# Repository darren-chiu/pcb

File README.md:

<b> PCB Repository meant to track and hold my PCB designs along with any code associated </b> <br/> <br/>
 Astromech Board -- STM32f405 and MPU6050 with darlington arrays for driving steppers

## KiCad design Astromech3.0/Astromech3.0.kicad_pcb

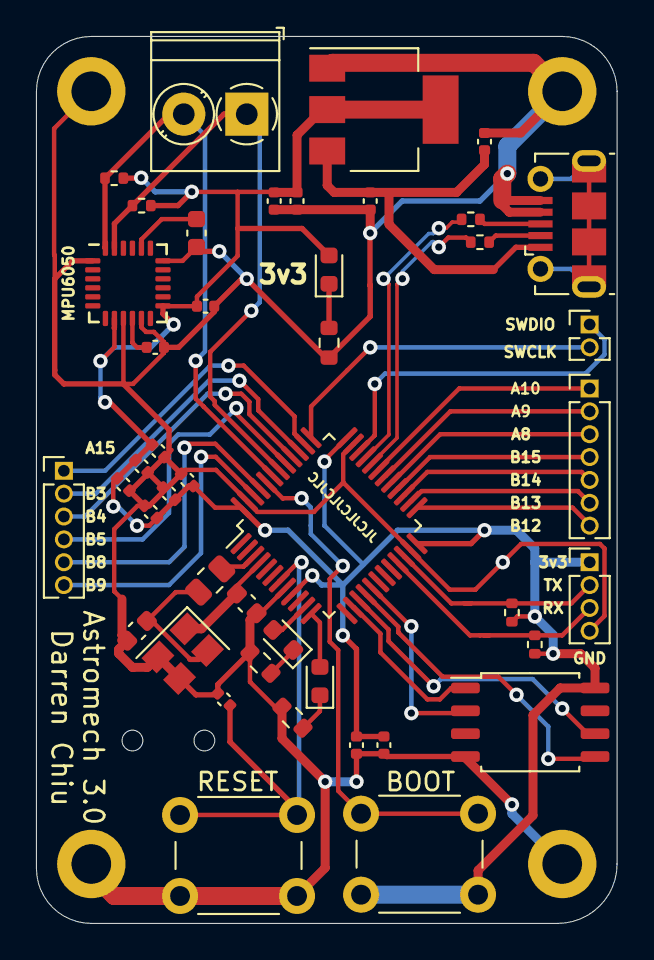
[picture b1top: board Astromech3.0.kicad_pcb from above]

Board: 2 copper layers, 32.3 x 49.3 mm, 48 parts (0 on the bottom side), 42 nets.

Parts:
C1, C4, C5, C6, C7, C9, C10, C11, C12: 100nF; C_0402_1005Metric
C2, C3: 12p; C_0603_1608Metric
C8, C17: 10uF; C_0402_1005Metric
C13, C15, C18, C19: 0.1uF; C_0402_1005Metric
C16: 2.2nF; C_0603_1608Metric
D1: RED; D_0603_1608Metric
D2: YELLOW; D_0603_1608Metric
D3: GREEN; D_0603_1608Metric
H1, H2, H3, H4: MountingHole_Pad; MountingHole_2.2mm_M2_DIN965_Pad
J1: Screw_Terminal_01x02; TerminalBlock_Phoenix_PT-1,5-2-3.5-H_1x02_P3.50mm_Horizontal
J2: Conn_01x02; PinHeader_1x02_P1.27mm_Vertical
J3: USB_B_Micro; USB_Micro-B_Molex-105017-0001
J4: Conn_01x04; PinHeader_1x04_P1.27mm_Vertical
J5: Conn_01x07; PinHeader_1x07_P1.27mm_Vertical
J6: Conn_01x06; PinHeader_1x06_P1.27mm_Vertical
R1, R2, R3, R4: 10k; R_0402_1005Metric
R5: 220; R_0805_2012Metric
R6, R7, R10: 510; R_0603_1608Metric
R8, R9: 22; R_0402_1005Metric
SW1, SW2: SW_Push; SW_PUSH_6mm
U1: STM32F103C8Tx; LQFP-48_7x7mm_P0.5mm
U2: MPU-6050; InvenSense_QFN-24_4x4mm_P0.5mm
U3: AMS1117; SOT-223-3_TabPin2
U4: W25Q128JVS; SOIC-8_5.23x5.23mm_P1.27mm
Y1: Crystal; Crystal_SMD_3225-4Pin_3.2x2.5mm

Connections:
+3V3: C1.1, C4.1, C5.1, C6.1, C7.1, C9.1, C11.1, C13.2, C17.1, C18.2, C19.2, D1.2, J4.1, R1.2, R2.2, R3.2, R4.2, SW2.2, U1.9, U1.24, U1.36, U1.48, U2.8, U2.13, U3.2, U4.8
+5V: C8.1, C12.1, J3.1, U3.3
BOOT0: SW2.1, U1.44
D+: R8.1, U1.33
D-: R9.1, U1.32
GND: C1.2, C2.1, C3.1, C4.2, C5.2, C6.2, C7.2, C8.2, C9.2, C10.2, C11.2, C12.2, C13.1, C15.1, C16.1, C17.2, C18.1, C19.1, H1.1, H2.1, H3.1, H4.1, J3.4, J3.5, J4.4, R6.1, R7.1, R10.1, SW1.1, U1.8, U1.23, U1.35, U1.47, U2.1, U2.9, U2.11, U2.18, U3.1, U4.4, Y1.2, Y1.3
I2C_SCL: J1.1, R3.1, U1.42, U2.23
I2C_SDA: J1.2, R4.1, U1.43, U2.24
unnamed: C2.2, R5.2, Y1.4
unnamed: C15.2, U2.10
unnamed: C16.2, U2.20
unnamed: D1.1, R6.2
unnamed: D2.1, R7.2
unnamed: D3.1, R10.2
unnamed: J3.2, R9.2
unnamed: J3.3, R8.2
OSC_IN: R5.1, U1.3
OSC_OUT: C3.2, U1.4, Y1.1
PA8: J5.3, U1.29
PA9: J5.2, U1.30
PA10: J5.1, U1.31
PA15: J6.1, U1.38
PB3: J6.2, U1.39
PB4: J6.3, U1.40
PB5: J6.4, U1.41
PB8: J6.5, U1.45
PB9: J6.6, U1.46
PB12: J5.7, U1.25
PB13: J5.6, U1.26
PB14: J5.5, U1.27
PB15: J5.4, U1.28
QSPI_CLK: U1.15, U4.6
QSPI_CS: U1.14, U4.1
RESET: C10.1, SW1.2, U1.7
SPI_MISO: U1.16, U4.5
SPI_MOSI: U1.17, U4.2
STATUS0: D3.2, U1.12
STATUS1: D2.2, U1.11
SWCLK: J2.2, U1.37
SWDIO: J2.1, U1.34
UART_RX: J4.3, R2.1, U1.21
UART_TX: J4.2, R1.1, U1.22

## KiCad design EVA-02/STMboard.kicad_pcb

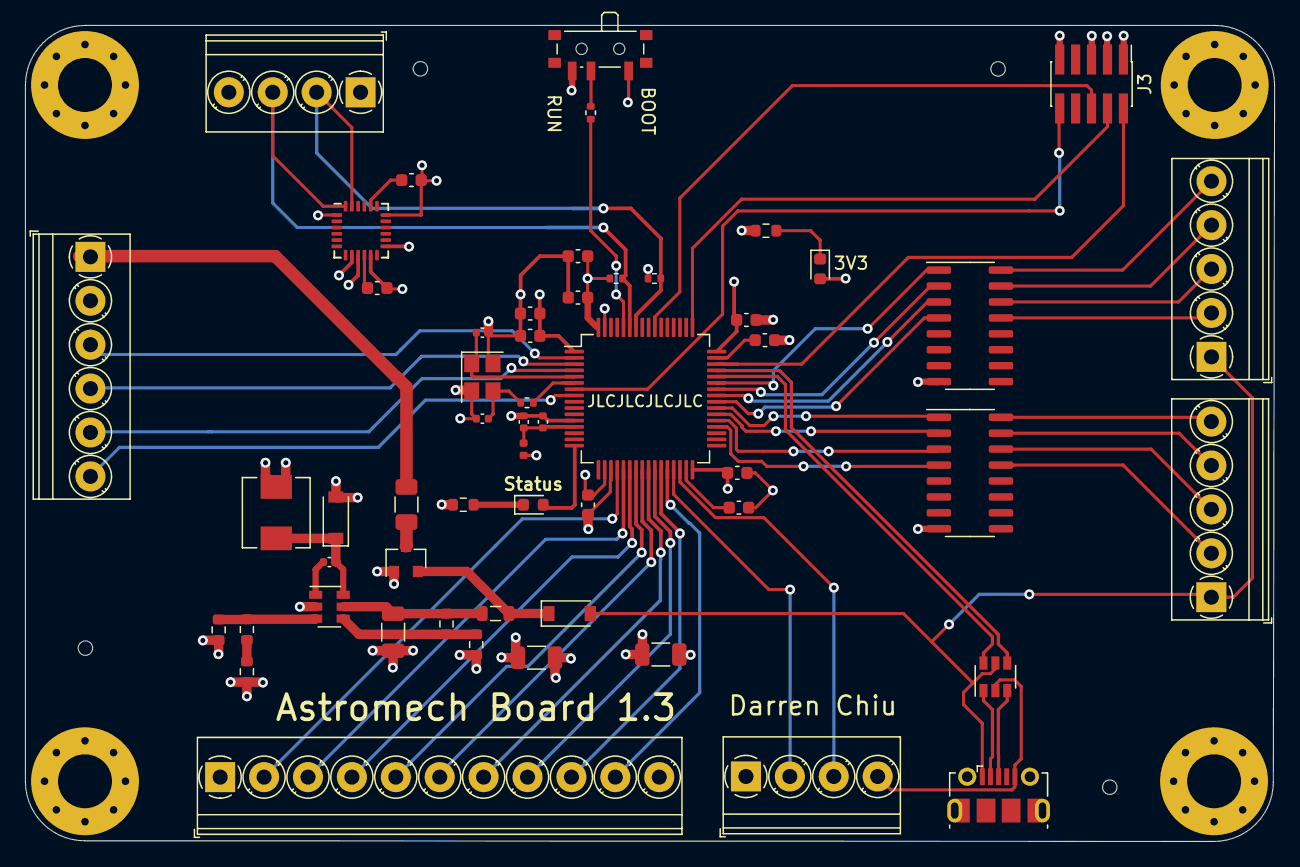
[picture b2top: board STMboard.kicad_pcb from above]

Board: 4 copper layers, 99.6 x 65.1 mm, 59 parts (0 on the bottom side), 66 nets.

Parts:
C1: 4u7; C_0603_1608Metric
C2, C4: 2.2u; C_0603_1608Metric
C3, C5, C6, C8, C9, C10, C11: 100nF; C_0603_1608Metric
C7, C14, C15: 10u; C_1206_3216Metric
C12: 2.2nF; C_0603_1608Metric
C13, C19: 10n; C_0402_1005Metric
C16, C18: 12p; C_0402_1005Metric
C17: 1u; C_0402_1005Metric
D1: BLUE; LED_0603_1608Metric
D2, D3: B5819W; D_SOD-123
D4: RED; LED_0603_1608Metric
F1: 250mA; Fuse_1206_3216Metric
FB1: 600 @ 600MHz; L_0805_2012Metric
H1, H2, H3, H4: MountingHole_Pad; MountingHole_4.3mm_M4_Pad_Via
HSE1: 16MHz; Crystal_SMD_3225-4Pin_3.2x2.5mm
J1: Screw_Terminal_01x06; TerminalBlock_Phoenix_PT-1,5-6-3.5-H_1x06_P3.50mm_Horizontal
J2: USB_B_Micro; USB_Micro-B_Molex-105017-0001
J3: Conn_02x05_Odd_Even; PinHeader_2x05_P1.27mm_Vertical_SMD
J4, J7: Screw_Terminal_01x04; TerminalBlock_Phoenix_PT-1,5-4-3.5-H_1x04_P3.50mm_Horizontal
J5, J8: Screw_Terminal_01x05; TerminalBlock_Phoenix_PT-1,5-5-3.5-H_1x05_P3.50mm_Horizontal
J6: Screw_Terminal_01x11; TerminalBlock_Phoenix_PT-1,5-11-3.5-H_1x11_P3.50mm_Horizont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
L1: 10u; L_Sunlord_MWSA0518_5.4x5.2mm
L2: 39n; L_0402_1005Metric
Q1: AO3401A; SOT-23
R1: 1k5; R_0603_1608Metric
R2: 10k; R_0402_1005Metric
R3: 100k; R_0603_1608Metric
R4: 68k; R_0603_1608Metric
R5, R6: 2k2; R_0402_1005Metric
R7: 47k; R_0603_1608Metric
R8: 15k; R_0603_1608Metric
R9: 270; R_0603_1608Metric
R10: 1k; R_0603_1608Metric
R11: 47; R_0402_1005Metric
SW1: SW_SPDT; SW_SPDT_PCM12
U1: STM32F405RGTx; LQFP-64_10x10mm_P0.5mm
U2: MP2359DJ-LF-Z; SOT-23-6
U3: MPU-6050; InvenSense_QFN-24_4x4mm_P0.5mm
U4: USBLC6-2SC6; SOT-23-6
U5, U6: ULN2003A; SOIC-16_3.9x9.9mm_P1.27mm

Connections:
+3.3VA: C17.1, C19.1, L2.2, U1.13
+3V3: C1.1, C3.1, C5.1, C6.1, C8.1, C9.1, C10.1, C14.1, C15.1, D4.2, J3.1, J4.1, J6.1, J7.1, L1.2, L2.1, R5.2, R6.2, R7.2, SW1.1, U1.1, U1.19, U1.32, U1.48, U1.64, U3.8, U3.13
+5V: D2.2, J2.1, J5.1, J8.1, U4.5
+12V: F1.2, J1.1
BOOT0: R2.2, U1.60
BUCK_BST: C13.1, U2.1
BUCK_EN: R3.1, R4.2, U2.4
BUCK_FB: R7.1, R8.2, U2.3
BUCK_IN: C7.1, FB1.1, R3.2, U2.5
BUCK_SW: C13.2, D3.1, L1.1, U2.6
GND: C1.2, C2.2, C3.2, C4.2, C5.2, C6.2, C7.2, C8.2, C9.2, C10.2, C11.2, C12.2, C14.2, C15.2, C16.2, C17.2, C18.2, C19.2, D3.2, H1.1, H2.1, H3.1, H4.1, HSE1.2, HSE1.4, J1.2, J2.5, J3.3, J3.5, J3.9, J4.4, J6.11, J7.4, Q1.1, R1.2, R4.1, R9.1, R10.1, SW1.3, U1.12, U1.18, U1.63, U2.2, U3.1, U3.9, U3.11, U3.18, U4.2, U5.8, U6.8
HSE_IN: C16.1, HSE1.1, U1.5
HSE_OUT: R11.1, U1.6
I2C1_SCL: J4.2, R5.1, U1.58, U3.23
I2C1_SDA: J4.3, R6.1, U1.59, U3.24
LED_STATUS: D1.2, U1.16
NRST: J3.10, U1.7
unnamed: C2.1, U1.31
unnamed: C4.1, U1.47
unnamed: C11.1, U3.10
unnamed: C12.1, U3.20
unnamed: C18.1, HSE1.3, R11.2
unnamed: D1.1, R1.1
unnamed: D2.1, FB1.2, Q1.2
unnamed: D4.1, R10.2
unnamed: F1.1, Q1.3
unnamed: J5.2, U5.13
unnamed: J5.3, U5.14
unnamed: J5.4, U5.15
unnamed: J5.5, U5.16
unnamed: J8.2, U6.13
unnamed: J8.3, U6.14
unnamed: J8.4, U6.15
unnamed: J8.5, U6.16
unnamed: R2.1, SW1.2
unnamed: R8.1, R9.2
PA4: J6.2, U1.20
PA5: J6.3, U1.21
PA6: J6.4, U1.22
PA7: J6.5, U1.23
PB0: J6.8, U1.26
PB1: J6.9, U1.27
PB2: J6.10, U1.28
PC4: J6.6, U1.24
PC5: J6.7, U1.25
PC8: J1.6, U1.8
PC13: J1.3, U1.2
PC14: J1.4, U1.3
PC15: J1.5, U1.4
STEP_1-1: U1.43, U5.1
STEP_1-2: U1.42, U5.2
STEP_1-3: U1.41, U5.3
STEP_1-4: U1.40, U5.4
STEP_2-1: U1.39, U6.1
STEP_2-2: U1.38, U6.2
STEP_2-3: U1.37, U6.3
STEP_2-4: U1.36, U6.4
SWCLK: J3.4, U1.49
SWDIO: J3.2, U1.46
SWO: J3.6, U1.55
UART3_RX: J7.3, U1.30
UART3_TX: J7.2, U1.29
USB_CONN_D+: J2.3, U4.3
USB_CONN_D-: J2.2, U4.1
USB_D+: U1.45, U4.4
USB_D-: U1.44, U4.6

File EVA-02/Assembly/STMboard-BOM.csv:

Comment,Designator,Footprint,LCSC
"4u7","C1","Capacitor_SMD:C_0603_1608Metric",""
"2.2nF","C12","Capacitor_SMD:C_0603_1608Metric",""
"10u","C7,C14,C15","Capacitor_SMD:C_1206_3216Metric",""
"12p","C16,C18","Capacitor_SMD:C_0402_1005Metric",""
"1u","C17","Capacitor_SMD:C_0402_1005Metric",""
"10n","C13,C19","Capacitor_SMD:C_0402_1005Metric",""
"2.2u","C2,C4","Capacitor_SMD:C_0603_1608Metric",""
"100nF","C3,C5,C6,C8,C9,C10,C11","Capacitor_SMD:C_0603_1608Metric",""
"BLUE","D1","LED_SMD:LED_0603_1608Metric",""
"B5819W","D2,D3","Diode_SMD:D_SOD-123",""
"RED","D4","LED_SMD:LED_0603_1608Metric",""
"250mA","F1","Fuse:Fuse_1206_3216Metric",""
"600 @ 600MHz","FB1","Inductor_SMD:L_0805_2012Metric",""
"MountingHole_Pad","H1,H2,H3,H4","MountingHole:MountingHole_4.3mm_M4_Pad_Via",""
"16MHz","HSE1","Crystal:Crystal_SMD_3225-4Pin_3.2x2.5mm",""
"Screw_Terminal_01x06","J1","TerminalBlock_Phoenix:TerminalBlock_Phoenix_PT-1,5-6-3.5-H_1x06_P3.50mm_Horizontal",""
"USB_B_Micro","J2","Connector_USB:USB_Micro-B_Molex-105017-0001",""
"Conn_02x05_Odd_Even","J3","Connector_PinHeader_1.27mm:PinHeader_2x05_P1.27mm_Vertical_SMD",""
"Screw_Terminal_01x04","J4,J7","TerminalBlock_Phoenix:TerminalBlock_Phoenix_PT-1,5-4-3.5-H_1x04_P3.50mm_Horizontal",""
"Screw_Terminal_01x05","J5,J8","TerminalBlock_Phoenix:TerminalBlock_Phoenix_PT-1,5-5-3.5-H_1x05_P3.50mm_Horizontal",""
"Screw_Terminal_01x11","J6","TerminalBlock_Phoenix:TerminalBlock_Phoenix_PT-1,5-11-3.5-H_1x11_P3.50mm_Horizontal",""
"10u","L1","Inductor_SMD:L_Sunlord_MWSA0518_5.4x5.2mm",""
"39n","L2","Inductor_SMD:L_0402_1005Metric",""
"AO3401A","Q1","Package_TO_SOT_SMD:SOT-23",""
"1k5","R1","Resistor_SMD:R_0603_1608Metric",""
"1k","R10","Resistor_SMD:R_0603_1608Metric",""
"47","R11","Resistor_SMD:R_0402_1005Metric",""
"10k","R2","Resistor_SMD:R_0402_1005Metric",""
"100k","R3","Resistor_SMD:R_0603_1608Metric",""
"68k","R4","Resistor_SMD:R_0603_1608Metric",""
"2k2","R5,R6","Resistor_SMD:R_0402_1005Metric",""
"47k","R7","Resistor_SMD:R_0603_1608Metric",""
"15k","R8","Resistor_SMD:R_0603_1608Metric",""
"270","R9","Resistor_SMD:R_0603_1608Metric",""
"SW_SPDT","SW1","Button_Switch_SMD:SW_SPDT_PCM12",""
"STM32F405RGTx","U1","Package_QFP:LQFP-64_10x10mm_P0.5mm",""
"MP2359DJ-LF-Z","U2","Package_TO_SOT_SMD:SOT-23-6",""
"MPU-6050","U3","Sensor_Motion:InvenSense_QFN-24_4x4mm_P0.5mm",""
"USBLC6-2SC6","U4","Package_TO_SOT_SMD:SOT-23-6",""
"ULN2003A","U5,U6","Package_SO:SOIC-16_3.9x9.9mm_P1.27mm",""

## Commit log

2020-12-25 Generated .net files
2020-12-26 Initial Board jpg
2020-12-29 Manufactured board files
2020-12-31 formatting change
2021-05-23 final manufactured board
2021-10-21 Hierarchical Added
